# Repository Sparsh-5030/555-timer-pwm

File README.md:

# 555-timer-pwm
This is a PCB schematic of 555 timer showing PWM output controlled by a potentiometer
it is created using KiCad 5.1

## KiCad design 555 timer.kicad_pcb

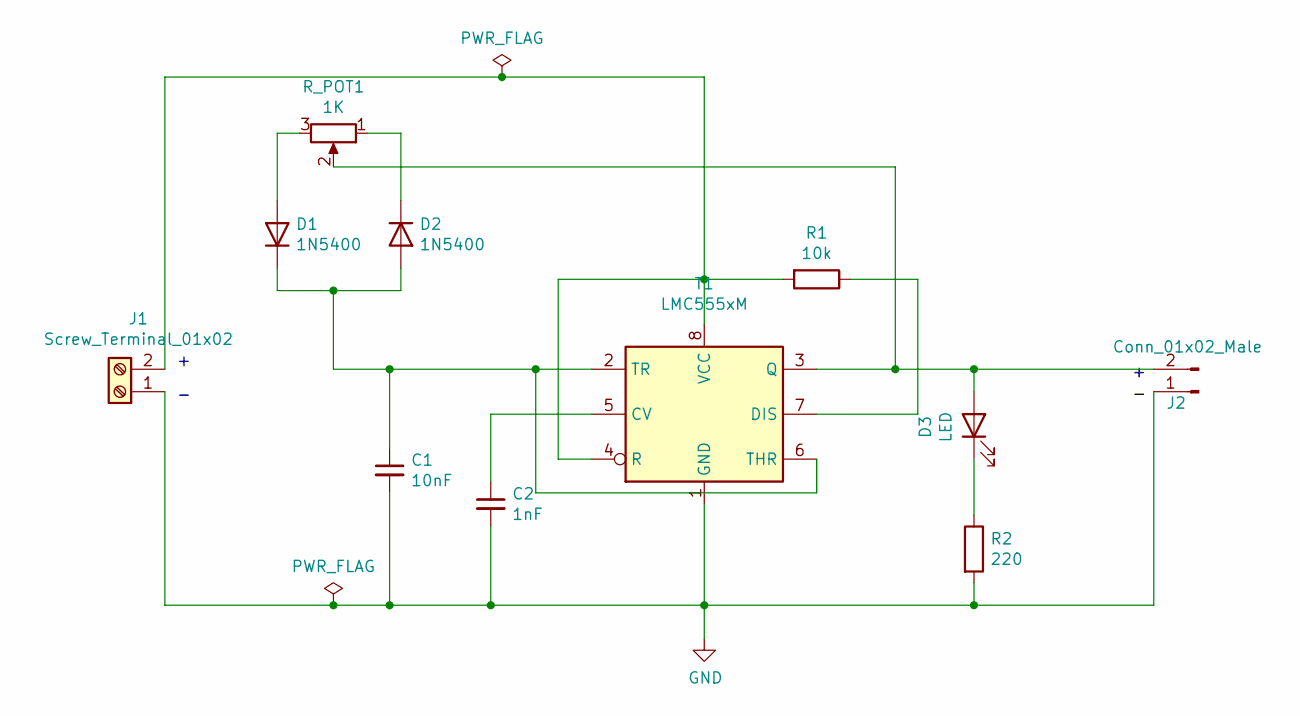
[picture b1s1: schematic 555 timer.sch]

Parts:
C1: 10nF; C_0805_2012Metric_Pad1.18x1.45mm_HandSolder
C2: 1nF; C_0805_2012Metric_Pad1.18x1.45mm_HandSolder
D1, D2: 1N5400; D_DO-41_SOD81_P10.16mm_Horizontal
D3: LED; LED_D3.0mm; digikey 404-1254-ND
J1: Screw_Terminal_01x02; PhoenixContact_MCV_1,5_2-G-5.08_1x02_P5.08mm_Vertical; digikey Phoenix Contact 1729128
J2: Conn_01x02_Male; PinSocket_1x02_P2.00mm_Vertical
R1: 10k; R_Axial_DIN0207_L6.3mm_D2.5mm_P10.16mm_Horizontal; digikey RC14JB1K00-ND
R2: 220; R_Axial_DIN0207_L6.3mm_D2.5mm_P10.16mm_Horizontal; digikey CFF14JT220R-ND
R_POT1: 1K; Potentiometer_Bourns_3339P_Vertical_HandSoldering
T1: LMC555xM; SOIC-8_3.9x4.9mm_P1.27mm; Digikey 296-40262-1-ND

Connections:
GND: C1.2, C2.2, J1.1, J2.1, R2.2, T1.1 (GND)
unnamed: C1.1, D1.1 (K), D2.2 (A), T1.2 (TR), T1.6 (THR)
unnamed: C2.1, T1.5 (CV)
unnamed: D1.2 (A), R_POT1.3
unnamed: D2.1 (K), R_POT1.1
unnamed: D3.1 (K), R2.1
unnamed: D3.2 (A), J2.2, R_POT1.2, T1.3 (Q)
unnamed: J1.2, R1.2, T1.4 (R), T1.8 (VCC)
unnamed: R1.1, T1.7 (DIS)

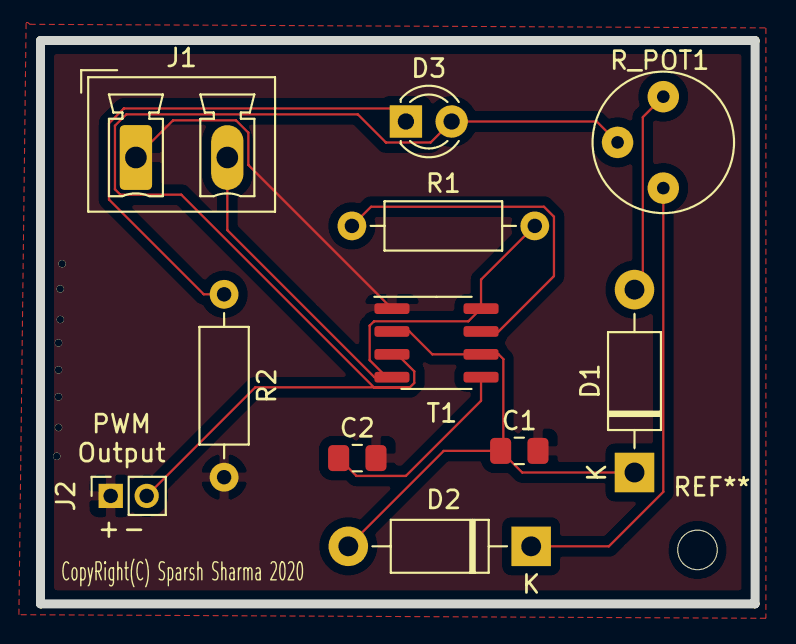
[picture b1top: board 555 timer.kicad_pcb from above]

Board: 2 copper layers, 39.7 x 31.3 mm, 11 parts (0 on the bottom side), 9 nets.

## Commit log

2020-11-20 Design modifications

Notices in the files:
555 timer.kicad_pcb:
CopyRight(C) Sparsh Sharma 2020
